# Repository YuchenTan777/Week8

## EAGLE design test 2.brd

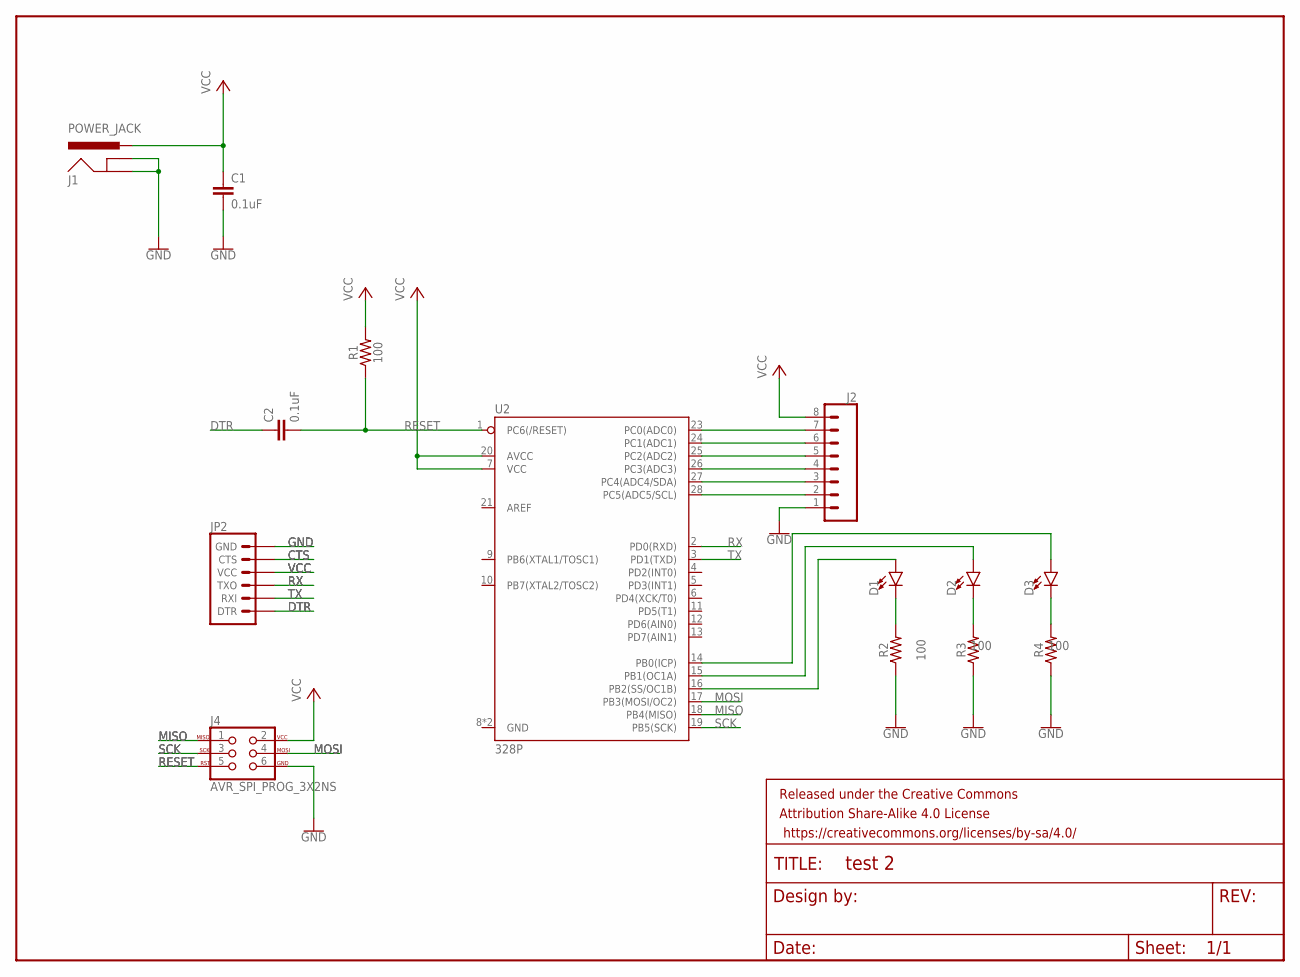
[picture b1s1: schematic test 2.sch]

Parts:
C1, C2: 0.1uF; 0402
D1, D2, D3: LED5MM; LED_5MM
FRAME1: FRAME-LETTER; CREATIVE_COMMONS
J1: POWER_JACK; POWER_JACK_PTH
J2: CONN_08BM08B-SRSS-TB; BM08B-SRSS-TB
J4: AVR_SPI_PROG_3X2NS; 2X3-NS
JP2: 6_PIN_SERIAL_TARGETLOCK; 1X06_LOCK
R1, R2, R3, R4: 100; 0603
U2: 328P; DIP28

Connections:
CTS: JP2.5 (CTS)
DTR: JP2.1 (DTR)
GND: C1.2, J1.GND, J1.GNDBREAK, J2.1, J4.6, JP2.6 (GND), R2.1, R3.1, R4.1
MISO: J4.1
MOSI: J4.4
unnamed: C2.2, R1.1, U2.1 (PC6(/RESET))
unnamed: J2.7, U2.23 (PC0(ADC0))
unnamed: J2.6, U2.24 (PC1(ADC1))
unnamed: J2.5, U2.25 (PC2(ADC2))
unnamed: J2.4, U2.26 (PC3(ADC3))
unnamed: J2.3, U2.27 (PC4(ADC4/SDA))
unnamed: J2.2, U2.28 (PC5(ADC5/SCL))
unnamed: D1.A, U2.16 (PB2(SS/OC1B))
unnamed: D2.A, U2.15 (PB1(OC1A))
unnamed: D3.A, U2.14 (PB0(ICP))
unnamed: D1.K (C), R2.2
unnamed: D2.K (C), R3.2
unnamed: D3.K (C), R4.2
RESET: J4.5
RX: JP2.3 (TXO)
SCK: J4.3
TX: JP2.2 (RXI)
VCC: C1.1, J1.PWR, J2.8, J4.2, JP2.4 (VCC), R1.2, U2.7 (VCC), U2.20 (AVCC)

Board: 2 copper layers, 15 parts (0 on the bottom side), 15 nets, no tracks yet.

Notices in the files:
parts and their libraries:
SparkFun-Capacitors: Licensing: Creative Commons ShareAlike 4.0 International - https://creativecommons.org/licenses/by-sa/4.0
SparkFun-Aesthetics: Released under the Creative Commons Attribution Share-Alike 4.0 License
SparkFun-Aesthetics: https://creativecommons.org/licenses/by-sa/4.0
